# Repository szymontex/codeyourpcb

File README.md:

# CodeYourPCB

**Code-first PCB design.** Describe your circuit board in a simple DSL — get a deterministic, git-friendly, AI-editable design.

```cypcb
// blink.cypcb — 555 timer LED blink circuit
version 1

board blink {
    size 60mm x 40mm
    layers 2
}

component J1 connector "PIN-HDR-1x2" { value "5V PWR"; at 5mm, 20mm }
component U1 ic "SOIC-8" { value "NE555"; at 28mm, 20mm }
component R1 resistor "0402" { value "10k"; at 35mm, 30mm }
component C1 capacitor "1206" { value "10uF"; at 43mm, 20mm }
component LED1 led "0805" { value "RED"; at 55mm, 20mm }

net VCC [width 0.5mm  current 2A] { J1.1; U1.8; U1.4; R1.1 }
net GND { J1.2; U1.1; C1.2; LED1.K }

// Routed traces saved in the file — survives reload, diffs cleanly
trace VCC {
    layer Top
    width 0.5mm
    path 5mm,20mm -> 15mm,20mm -> 28mm,20mm -> 35mm,30mm
}
```

Save the file, board updates instantly. No compile step, no refresh.

**New here?** [Syntax reference](docs/SYNTAX.md) | [Getting started](docs/user-guide/getting-started.md) | [Examples](examples/)

---

## Why?

Traditional PCB tools (KiCad, Altium, Eagle) are GUI-first. The project file is a binary/XML side-effect of clicking. This makes:

- **Git diffs** unreadable
- **AI assistance** impractical
- **Team review** painful
- **Automation** fragile

CodeYourPCB flips the model: the source file _is_ the design. Text in, board out.

## The LLM angle

The core idea: give AI coding assistants like Claude Code, Copilot, or Cursor the ability to **design real PCBs through declarative code** — the same way they write software.

Traditional PCB formats are opaque to LLMs. A KiCad `.kicad_pcb` file is thousands of lines of coordinate soup. No LLM can reason about that meaningfully.

`.cypcb` is different — the semantics are declarative and human-readable:

```cypcb
component U1 ic "SOIC-8" { value "NE555"; at 28mm, 20mm }
net VCC [width 0.5mm  current 2A] { U1.8; U1.4; R1.1 }

trace VCC {
    layer Top
    width 0.5mm
    path 5mm,20mm -> 28mm,20mm -> 35mm,30mm
}
```

An LLM can generate this, review it, refactor it, and catch mistakes — just like source code. Even routed traces are human-readable `path` blocks that diff cleanly in git.

---

## Features

| Feature | Status |
|---------|--------|
| `.cypcb` DSL, read by a hand-written Rust parser | Done — the default since the C parser stopped reaching WASM; `--features tree-sitter-parser` builds the grammar instead and a differential test reads every example with both and compares the ASTs. `docs/one-parser.md` has the measurement behind the choice |
| Live preview — save file, board updates instantly | Done |
| 2D renderer (KiCad-style) | Done |
| 3D viewer — extruded copper, solder mask, round trace caps | Done |
| Interactive trace routing (45° constraint, obstacle dodge) | Done |
| Trace segment & corner editing (drag to reshape) | Done |
| Trace persistence — routed traces saved as `path` blocks, survive reload | Done |
| Bidirectional sync — edit trace code ↔ board updates in real-time | Done |
| Net constraints — `[width 0.5mm]`, `[current 2A]` per net | Done |
| IPC-2221 auto-width from current rating | Done |
| DRC — every rule in the registry: `grep -o 'Box::new(rules::[A-Za-z]*' crates/cypcb-drc/src/lib.rs` names them, because a list written here goes stale the next time one is added | Done — `grep -c 'Box::new(rules::' crates/cypcb-drc/src/lib.rs` counts them, because a number written here goes stale the next time one is added; `cypcb check` prints copper-on-copper apart from a gap under spec, gives an orphaned plane its size and corners, and says when a rule's number is this tool's own rather than the fab's |
| DRC — silkscreen clearance | Done — a Rust rule checks a footprint's own artwork against every other part's pads on the same side |
| Gerber / Excellon / BOM / pick-and-place export | Done — with a Gerber job file (`<board>-job.gbrjob`) at the root of the output, naming every Gerber and drill file, what each one is, its format and, for the images, its polarity - plus board size, layer count and, when the design declares a stackup, the material stackup and board thickness. Each file states its own function in its header and the job file reads it back, so the two cannot disagree |
| Monaco editor with context-aware completions | Done |
| JLCPCB parts search & placement | Done |
| Custom footprint definitions in DSL | Done |
| Project manager with templates | Done |
| Dark / Light theme | Done |
| Web app (WASM) | Done |
| Desktop app (Tauri v2) | Builds on macOS and Windows; the Linux build needs the GTK/webkit dev packages listed under Quick Start. Nothing here runs in CI, because there is none |
| Autorouter — PathFinder negotiated congestion, multi-layer | Routes the benchmark boards complete; **the toolbar button is hidden** while routing quality is worked on |
| KiCad component library import | Done |
| KiCad `.kicad_pcb` import | Done — `cypcb parse-kicad`, used by the routing benchmarks. Reads KiCad 5 through 10, including the tableless net form KiCad 10 introduced, where a pad names its net directly instead of pointing into a table |
| KiCad `.kicad_pcb` import to the language | Done — `cypcb from-kicad <board>.kicad_pcb` writes a `.cypcb` design: the board, a declared outline when it is not a plain rectangle, a `footprint` definition per part KiCad names, one `component` each with its value, placement, rotation and side, a `net` block per net, and the routed copper. The command re-reads what it wrote before reporting success. What a part *is* comes from its reference designator prefix, because KiCad does not record it, and `generic` where the prefix says nothing. A copper pour comes back as a `zone` block with the net and the layer it was poured on, named after that net where KiCad named it - `zone GND` bare and `zone "VBUS+"` quoted, because the language takes both; a board whose pads are named rather than numbered - a USB-C receptacle's A1, B4, S1 - comes back carrying those names, and a net called `VBUS+` or `D-` comes back quoted, because the language takes both and renaming either would move pins onto the wrong nets |
| KiCad `.kicad_pcb` export | Done — `cypcb to-kicad --preset <fab>` writes the outline, a footprint per part with its pads, nets and the face it is soldered to, every trace and via, the net list, every copper pour and keepout, the board thickness the design states, and a legend per part - its own artwork when the footprint has any, its courtyard outline when it does not, the same rule the Gerber writer follows. Free silkscreen text and 3D models are not written; KiCad fills its own defaults for what a file leaves out. With `--preset` it also writes the `.kicad_pro` beside the board, because that is where KiCad keeps design rules - a board file stating them is a board file pcbnew refuses to open. Open the board through that file and KiCad's own DRC measures it against the fab the design was checked for |
| Copper pour / ground planes | Done — a zone is filled against the copper on its layer, with the fab's clearance to foreign copper and thermal spokes to its own pads. The same geometry reaches the Gerbers, the viewer and the checker, which reports two planes shorted together and copper the fill left connected to nothing. See `examples/pour-island.cypcb` |
| Module system — reusable circuit blocks | Done — `module` defines one, `use M as N at 10mm, 5mm` places it, modules nest. See `examples/v2-modules.cypcb` |
| `import` — block libraries across files | Done — resolved relative to the importing file; modules, footprints and interfaces cross, a design's own board and parts do not. See `examples/v2-imports.cypcb` |
| `assert` — the design's own claims, checked | Done — `board.*`, `<part>.value` and `<net>.current/width/clearance`; anything else is reported as not checked rather than skipped |
| Parts engine — auto component picking from JLCPCB/LCSC | Partly — a design names the part with `lcsc "C7593"`, the viewer fetches that part's real footprint, and the bill of materials carries it in JLCPCB's own `LCSC Part #` column. Picking a part for you is planned |
| Two-sided assembly | Partly — `side bottom` on a component flips it onto the back of the board: its copper, solder mask, paste and silkscreen all move with it and the pick-and-place list says `Bottom`. The browser draws its legend in the bottom silkscreen colour and its pads on the bottom copper |
| Schematic generation from `.cypcb` | Planned |
| Differential pairs | Declared and checked — `diffpair USB { USB_DP USB_DM }`, and the checker measures the skew between the halves against the fab's length-match tolerance. Routing them alongside each other, and the gap between them, are still planned |
| CI/CD in GitHub Actions | Not planned — the quality gate is `scripts/quality-gate.sh`, run locally |

Routing quality on the six bundled KiCad benchmarks. The numbers move whenever
the router or the checker changes, so they are not written down here - this
prints them:

```bash
cargo test --release -p cypcb-autoroute --test benchmark_validation \
    -- benchmark_all_fixtures_drc --ignored --nocapture
```

Each line reads `N routes, V violations against R, S shorts against T, U
unrouted`, where `R` and `T` are ratchets: the values the board is not allowed
to exceed, declared in `DRC_RATCHETS` in that test and lowered as the router
improves. Every board routes to completion - `U` is 0 on all six, and that is
asserted, not observed.

A table of these numbers lived here and every row of it had gone stale: it
listed three of the six boards and figures the checker had since moved twice,
once by measuring copper instead of part bodies and once by seeing footprints
on imported boards at all. `docs/TRACKER.md` records each change with what it
moved.

`cypcb route` routes the board eleven ways and keeps the best,
because no one setting wins everywhere - measured across the six benchmark
boards, the winner differs between them. It costs roughly eleven times the wall
clock of a single run and buys, on `examples/blink.cypcb`, 2 violations with 2 shorts
against 4 with 3. `--fast` routes once when the wait matters more than the
board.

---

## Quick Start

### Web (development)

```bash
git clone https://github.com/szymontex/codeyourpcb.git
cd codeyourpcb
./scripts/setup-dev.sh   # Rust target, wasm-bindgen at the pinned version, binaryen, browsers

cd viewer
npm install
npm start                # builds WASM + starts dev server
```

**Prerequisites**: Rust (stable), Node.js 18+, and two tools the WASM build
runs directly - the `wasm-bindgen` CLI and `wasm-opt` from binaryen.
`./scripts/setup-dev.sh` installs both and is safe to run again; every step
checks before it installs. By hand:

```bash
# wasm-bindgen must match the version Cargo.lock pins, or the bindings it
# writes will not load the module the build produced.
cargo install wasm-bindgen-cli --version \
  "$(grep -A1 '^name = "wasm-bindgen"$' Cargo.lock | grep '^version' | cut -d'"' -f2)"

# binaryen, for wasm-opt. The build refuses to run without it rather than
# shipping a module a third larger.
sudo apt install binaryen     # Debian/Ubuntu
brew install binaryen         # macOS
```

`cargo binstall wasm-bindgen-cli --version ...` fetches a prebuilt binary where
`cargo install` compiles it from source; `cargo install
cargo-binstall` first, and fall back to `cargo install` on a platform it has no
build for.

**`wasm-pack` is not used.** `viewer/build-wasm.sh` runs cargo, wasm-bindgen
and wasm-opt as three steps of its own, because wasm-pack 0.14 cannot be told
about this project's `wasm-release` profile and runs a `wasm-opt -O` that
refuses the module. The script says so at the top.

Open http://localhost:4321 — pick a template or open a `.cypcb` file.

To reach that server from another machine, name the host it will answer to:
`CYPCB_DEV_HOSTS=board.example.lan npm start`. Vite refuses a `Host` header it
was not told about, and the list is empty by default, so without this you get a
bare 403 from your own dev server.

### Desktop app (Tauri)

```bash
# Linux prerequisites
sudo apt install libwebkit2gtk-4.1-dev libgtk-3-dev libayatana-appindicator3-dev librsvg2-dev pkg-config

npm run dev:desktop   # dev mode
npm run build:desktop # release installer
```

### CLI

```bash
cargo run -p cypcb-cli -- check examples/blink.cypcb          # DRC, exit 1 on violations
cargo run -p cypcb-cli -- export examples/blink.cypcb -o out    # refuses a shorted board unless --force
cargo run -p cypcb-cli -- route examples/blink.cypcb --variants   # route, keep the best
cargo run -p cypcb-cli -- score examples/blink.routed.cypcb   # quality metrics as JSON
cargo run -p cypcb-cli -- export examples/blink.cypcb         # 14 manufacturing files
cargo run -p cypcb-cli -- parse examples/blink.cypcb          # the board, as JSON
cargo run -p cypcb-cli -- parse examples/blink.cypcb -o ast    # the AST instead
cargo run -p cypcb-cli -- parse-kicad tests/fixtures/benchmark/led_blink.kicad_pcb   # a KiCad board
cargo run -p cypcb-cli -- to-kicad examples/blink.cypcb       # the design as a KiCad board
cargo run -p cypcb-cli -- from-kicad tests/fixtures/benchmark/led_blink.kicad_pcb   # a KiCad board as a design
cargo run -p cypcb-cli -- watch examples/blink.cypcb          # check again on every save
```

`check`, `route` and `score` all take `--preset`, and an unknown
name prints the list. Without it they read the board's own `fab`, for its layer
count; the `fab` section of `docs/SYNTAX.md` says which table that is. They use
the same rules and agree on the same board:
`examples/blink.routed.cypcb` is 2 violations to `check --preset pcbway` and 2
to `score --preset pcbway`.

On an **unrouted** file they will not agree, and that is not a disagreement
about the rules. `score` routes the board before measuring it, so it reports
what its own routing came to - `examples/blink.cypcb` is 24 violations to
`check` and 4 to `score`, because the second one laid copper first - three of
those four are corners the router drew itself.

`--preset` means two things, though, and the lists are not the same length.
`check`, `route` and `score` take a **design-rule** preset - what a house can
etch - and know eleven: `jlcpcb_standard_2layer`, `jlcpcb_standard_4layer`,
the two advanced variants, `pcbway_standard`, `oshpark_2layer`,
`oshpark_4layer`, `ipc_class1`, `ipc_class2`, `ipc_class3` and `prototype`,
with `jlcpcb`, `oshpark`, `pcbway` and `ipc1`..`ipc3` as short forms that name
what they resolved to. `export` takes a **file convention** preset - what a
house wants the Gerbers called and in what coordinate format - and only
`jlcpcb` and `pcbway` have been written down. So a board can be checked
against OSHPark and not yet exported for it; `cypcb export --house oshpark`
says exactly that.

### IDE workflow

Edit `.cypcb` files in your editor (VS Code, Neovim, etc.). Run `npm run dev:watch` in a terminal — the board preview updates on every save via WebSocket hot reload.

---

## Keyboard Shortcuts

| Key | Action |
|-----|--------|
| `Ctrl+E` | Toggle code editor |
| `Ctrl+S` | Save file |
| `Ctrl+O` | Open file / project manager |
| `Ctrl+J` | JLCPCB parts search |
| `Ctrl+Z` / `Ctrl+Shift+Z` | Undo / Redo |
| `F` | Fit board to view |
| `3` | Toggle 3D view |
| `R` / `Shift+R` | Rotate component CW / CCW |
| `?` | Keyboard shortcuts help |

During trace routing: `F` flip layer, `/` flip posture, `Q` toggle corner mode, `A` toggle angle snap.

---

## Project Structure

```
codeyourpcb/
├── crates/
│   ├── cypcb-core         # Types, coordinates, units
│   ├── cypcb-parser       # Rust reader (default) + Tree-sitter grammar
│   ├── cypcb-world        # ECS board state (bevy_ecs)
│   ├── cypcb-drc          # Design rule checks
│   ├── cypcb-autoroute    # A*-based autorouter (WIP)
│   ├── cypcb-router       # Route application, and the DSN/SES bridge
│   ├── cypcb-calc         # Electrical calculations (IPC-2221)
│   ├── cypcb-export       # Gerber / Excellon / CPL export
│   ├── cypcb-kicad        # KiCad format import and export
│   ├── cypcb-library      # Component library (SQLite + FTS5)
│   ├── cypcb-lsp          # Language server (tower-lsp)
│   ├── cypcb-render       # Board engine (WASM)
│   ├── cypcb-rules        # Design rules & manufacturer presets
│   ├── cypcb-platform     # Native/web abstraction layer
│   ├── cypcb-watcher      # File system watcher
│   └── cypcb-cli          # CLI entry point
├── viewer/                # TypeScript frontend (Vite + Canvas 2D + Three.js)
├── src-tauri/             # Tauri v2 desktop shell
├── examples/              # Sample .cypcb files
└── docs/                  # User guide, syntax, API reference
```

---

## Landscape

CodeYourPCB sits in the emerging "PCB as code" space alongside a few other tools:

- **[JITX](https://www.jitx.com/)** — commercial, most mature code-first EDA. Constraint-driven routing, signal integrity, VS Code integration. Proprietary.
- **[atopile](https://atopile.io/)** — open-source `.ato` language with compiler, reusable modules, component picking. Uses KiCad for layout. MIT.
- **[tscircuit](https://tscircuit.com/)** — open-source React/TypeScript PCB framework. Very LLM-friendly (TypeScript is natural for models). MIT.

Where CodeYourPCB differs: own rendering engine (no KiCad dependency), runs in browser via WASM, interactive routing built-in, traces persist as readable DSL code. Where it's behind: no schematic capture, smaller component library.

---

## Documentation

- [Getting Started](docs/user-guide/getting-started.md)
- [Language Syntax](docs/SYNTAX.md)
- [Architecture](docs/architecture.md)
- [Routing](docs/routing.md) - what the autorouter does, the settings that pay, and the seventeen measured and dropped
- [One parser](docs/one-parser.md) - why the language is read twice, what each way of fixing that costs, and which one was chosen
- [Project Structure](docs/user-guide/project-structure.md)
- [Library Management](docs/user-guide/library-management.md)
- [Platform Differences (Web vs Desktop)](docs/user-guide/platform-differences.md)
- [Language server](docs/language-server.md) - the `cypcb-lsp` binary: what it answers, what it does not, and how to point an editor at it
- [Editor features in the browser](docs/api/lsp-server.md) - the WASM bridge that gives the built-in editor its diagnostics, without a server process
- [Contributing](CONTRIBUTING.md)

---

## Status

Experimental. The DSL and file format may change between versions.

The core loop works: write `.cypcb` → see board → route traces → save → reload
→ export. Traces are deterministic and a saved board reads back as the board
it was, which is checked end to end: routed copper reaches the Gerbers, the
cut path matches the outline the source declares, the mask opens over every
pad and the pick-and-place names the side each part is assembled on.

A copper pour is filled by the engine and drawn from it: the viewer sends the
zones it parsed and gets back the rectangles a fabricator receives, so the
screen cannot disagree with the Gerber. Keepouts are outlined, and copper a
pour left stranded is outlined too, because an island looks exactly like the
rest of the plane.

The main gap is the autorouter: its toolbar button stays hidden while routing
quality is worked on. `interface` is no longer one - a module that claims an
interface nobody defined, or claims one and does not expose all of its pins, is
reported by name.

PRs welcome.

---

## License

Licensed under either of:

- [MIT License](LICENSE-MIT)
- [Apache License, Version 2.0](LICENSE-APACHE)

at your option.

Copyright 2026 Szymon Gwóźdź. See [NOTICE](NOTICE).

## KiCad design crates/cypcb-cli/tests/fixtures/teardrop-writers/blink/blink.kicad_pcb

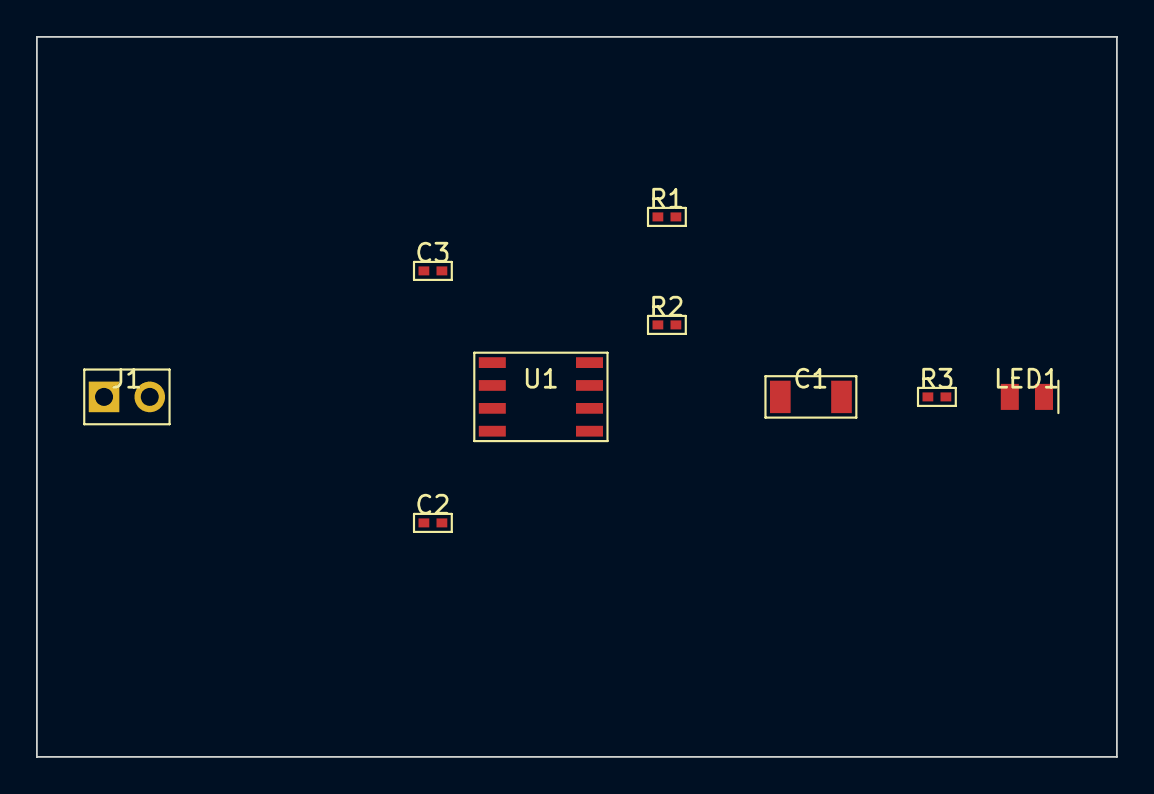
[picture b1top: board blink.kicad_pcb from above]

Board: 2 copper layers, 60.0 x 40.0 mm, 9 parts (0 on the bottom side), 7 nets, no tracks yet.

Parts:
C1: 10uF; 1206
C2, C3: 100nF; 0402
J1: 5V PWR; PIN-HDR-1x2
LED1: RED; LED_0805
R1: 10k; 0402
R2: 47k; 0402
R3: 470R; 0402
U1: NE555; SOIC-8

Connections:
CV: C2.1, U1.5
DIS: R1.2, R2.1, U1.7
GND: C1.2, C2.2, C3.2, J1.2, LED1.K, U1.1
LED_ANODE: LED1.A, R3.2
OUT: R3.1, U1.3
TRG_THR: C1.1, R2.2, U1.2, U1.6
VCC: C3.1, J1.1, R1.1, U1.4, U1.8

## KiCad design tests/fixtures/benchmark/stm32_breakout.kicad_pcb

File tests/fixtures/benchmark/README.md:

# Benchmark Fixtures

KiCad 8 PCB benchmark files for autorouter validation. Each file uses `(version 20240108)` format with the `footprint` keyword (KiCad 7/8 style).

## Fixtures

### led_blink.kicad_pcb — Simple

- **Source:** Synthetic (hand-crafted for benchmark suite)
- **License:** Same as project (MIT-equivalent)
- **Original project:** N/A — realistic LED blink circuit
- **Complexity tier:** Simple
- **Components:** 7 (1 connector, 1 switch, 2 capacitors, 2 resistors, 1 LED)
- **Nets:** 7 (VCC, GND, LED_ANODE, BATT_POS, SW_OUT, R_LED, BYPASS)
- **Layers:** 2 (F.Cu, B.Cu)
- **Board size:** 40×30 mm
- **Traces:** 3 segments, 2 vias

### stm32_breakout.kicad_pcb — Medium

- **Source:** Synthetic (hand-crafted for benchmark suite)
- **License:** Same as project (MIT-equivalent)
- **Original project:** N/A — realistic STM32F103C8T6 breakout board
- **Complexity tier:** Medium
- **Components:** 29 (1 MCU, 1 regulator, 1 USB-C, 1 ESD protection, 1 crystal, 1 switch, 2 GPIO headers, 1 SWD header, 11 capacitors, 7 resistors, 2 LEDs)
- **Nets:** 40 (power rails, GPIO PA0-PA7/PB0-PB7/PC13-PC15, USB, SWD, I2C, SPI, UART, ADC)
- **Layers:** 2 (F.Cu, B.Cu)
- **Board size:** 75×65 mm
- **Traces:** 8 segments, 4 vias

### multi_ic.kicad_pcb — Complex

- **Source:** Synthetic (hand-crafted for benchmark suite)
- **License:** Same as project (MIT-equivalent)
- **Original project:** N/A — realistic STM32F407 + Ethernet PHY + SPI Flash + CAN board
- **Complexity tier:** Complex
- **Components:** 52 (1 MCU LQFP-100, 1 Ethernet PHY QFN-24, 1 SPI Flash SOIC-8, 2 voltage regulators, 1 CAN transceiver, 1 USB ESD, 2 crystals, 1 Ethernet magnetics, 5 connectors, 1 ferrite bead, 1 reset switch, 5 LEDs, 12 resistors, 18 capacitors)
- **Nets:** 94 (3 power rails, 48 GPIO, USB, Ethernet RMII, SPI Flash, CAN, I2C, UART, SWD, ADC, oscillator)
- **Layers:** 4 (F.Cu, In1.Cu, In2.Cu, B.Cu)
- **Board size:** 100×80 mm
- **Traces:** 15 segments, 10 vias

### shift_driver.kicad_pcb — Medium

- **Source:** Generated by `make_shift_driver.py` in this directory
- **License:** Same as project (MIT-equivalent)
- **Original project:** N/A — three 74HC595 shift registers driving 24 LEDs
- **Complexity tier:** Medium
- **Components:** 55 (3 DIP-16 shift registers, 24 resistors, 24 LEDs, 3 bypass capacitors, 1 six-pin header)
- **Nets:** 55 (VCC, GND, SER, SRCLK, RCLK, 2 chain links, 24 drive, 24 anode)
- **Layers:** 2 (F.Cu, B.Cu)
- **Board size:** 68×48 mm
- **Traces:** none — it ships unrouted, which is what a routing benchmark wants

Added 2026-08-08. The three fixtures above are what every routing conclusion in
`docs/routing.md` was drawn from, and two of them are dense in the same way, so
a setting that happened to suit them could not be told from one that is right.
This board was generated rather than hand-placed so its provenance is
checkable: `make_shift_driver.py` declares the circuit as parts and nets and
knows nothing about the router. Through-hole DIP beside 0805 chips is a mix the
other three do not have.

It reports nothing but its own outline before routing — no courtyard overlap,
no pad-to-pad clearance, no mask bridge. The placement was spaced until that
was true, because a benchmark whose parts collide measures the router on a
board nobody would fabricate.

To regenerate: `python3 tests/fixtures/benchmark/make_shift_driver.py`

### qfp_fanout.kicad_pcb — Complex

- **Source:** Generated by `make_qfp_fanout.py` in this directory
- **License:** Same as project (MIT-equivalent)
- **Original project:** N/A — one LQFP-64 escaping to headers
- **Complexity tier:** Complex
- **Components:** 19 (1 LQFP-64, 11 capacitors, 2 resistors, 1 crystal, 4 twelve-pin headers, one per edge)
- **Nets:** 50 (VCC, GND, NRST, XTAL_IN, XTAL_OUT, BOOT, 44 GPIO)
- **Layers:** 2 (F.Cu, B.Cu)
- **Board size:** 46×46 mm
- **Traces:** none — it ships unrouted

Added 2026-08-08. The four boards above leave one regime untouched: a
fine-pitch part on two layers. `stm32_breakout` has a TQFP at 0.8mm pitch and
`multi_ic` an LQFP-100 on four layers with room to escape into; getting 64 pins
out at 0.5mm pitch with only a top and a bottom is what a two-layer router is
hardest on. It is the hardest of the five by some way — 665 introduced violations against
`multi_ic`'s 247 — and, like `shift_driver`, it reports nothing but its own
outline before routing.

Its first version put the GPIO on two twenty-one-pin headers down the sides.
That is 50.8mm of pins on a 46mm board, so three pads per header sat past the
outline and the router was being scored on a board nobody could make. A 46mm
edge holds fifteen pins once margins are taken, so two sides cannot hold
forty-eight: the headers are one per edge now, and no pad is outside the
outline.

Both generators share `kicad_emit.py`, which knows the file format and nothing
about the router.

To regenerate: `python3 tests/fixtures/benchmark/make_qfp_fanout.py`

### esp32_starter.cypcb - Medium, written in this language

- **Source:** Written by hand in `.cypcb`, not read from KiCad. The file's own header names the public datasheet behind every pin and value, with the date it was read
- **License:** Same as project (MIT-equivalent)
- **Original project:** N/A - an ESP32-S3-WROOM-1 starter board: USB-C in, AP2112K 3.3V regulator, BOOT and RESET buttons, two LEDs, two 1x12 GPIO headers
- **Complexity tier:** Medium
- **Components:** 18
- **Layers:** 2 (F.Cu, B.Cu)
- **Board size:** 34x50 mm
- **Traces:** none - the router lays them
- **Guarded by:** `cargo test -p cypcb-cli --test the_esp32_starter_is_a_board` - it parses, every part has a footprint, the module, receptacle and regulator pins are on the nets their datasheets name, and it routes. `cargo test -p cypcb-render --test esp32_starter_footprints_follow_their_datasheets` holds the four footprints to the figures of the pages the header cites, and `--test esp32_starter_routes_all_but_one_pin` holds the router to at most one open pin

## Usage

These files are parsed by `cypcb-kicad::pcb_parser::parse_kicad_pcb()` and used as benchmark inputs for:
- Parser correctness validation (`benchmark_parse.rs` integration tests)
- Autorouter performance benchmarking (S03/S07)
- Ratsnest extraction compatibility testing

## Format Notes

All files use KiCad 8 format (`version 20240108`) with:
- `footprint` keyword (not legacy `module`)
- `property` keyword for Reference/Value (not legacy `fp_text`)
- Realistic footprint library names (e.g., `Resistor_SMD:R_0402_1005Metric`)
- Proper layer assignments and net declarations

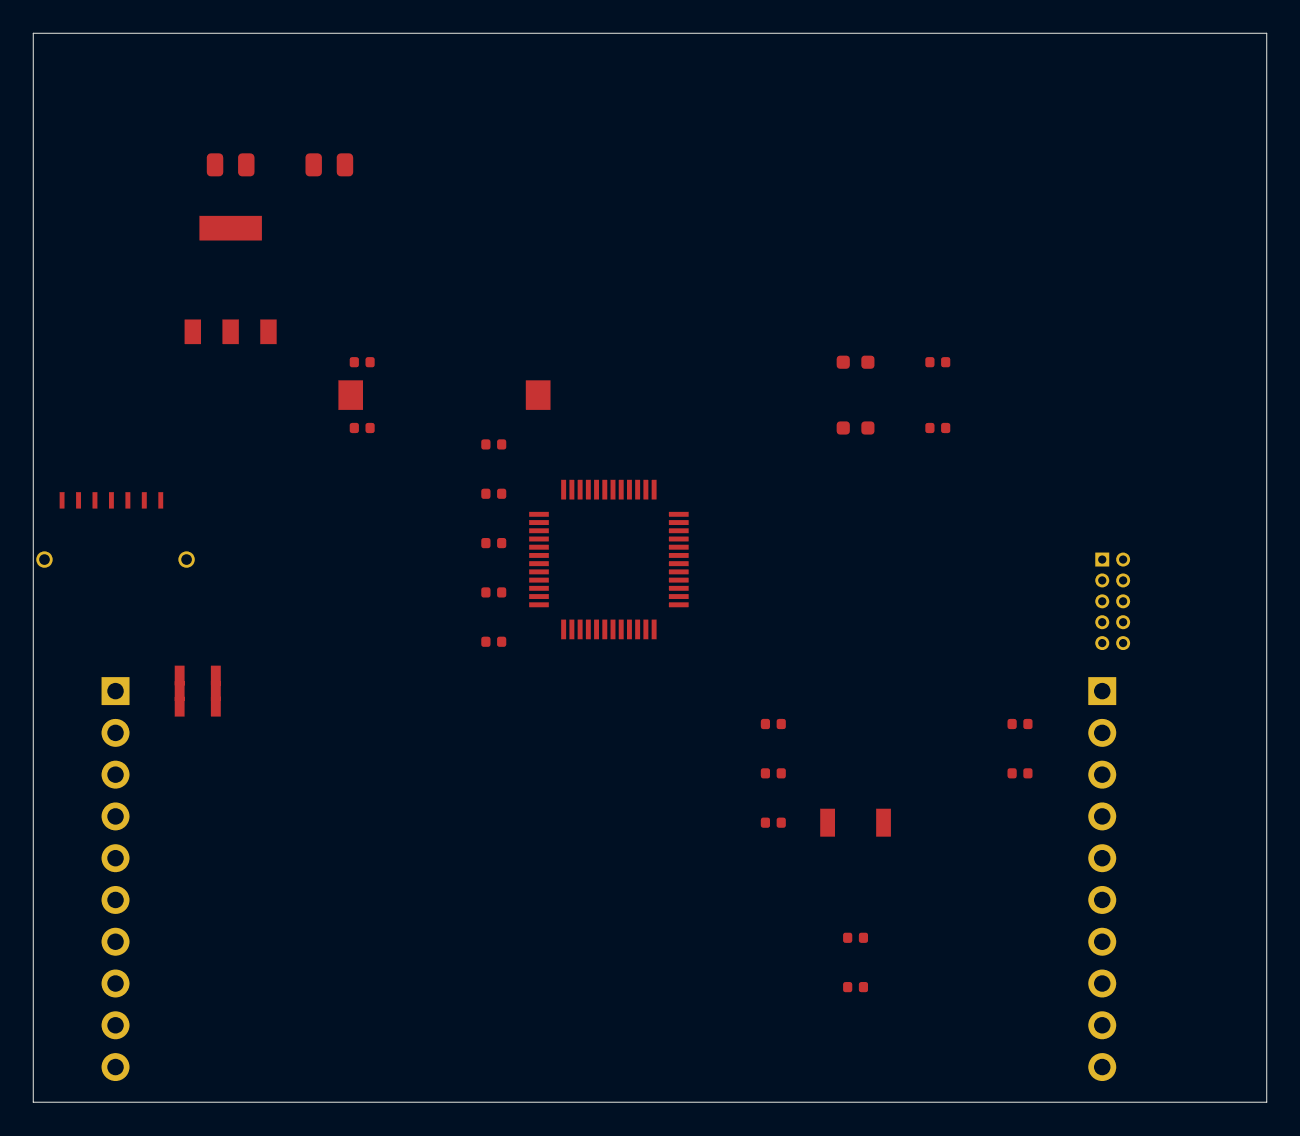
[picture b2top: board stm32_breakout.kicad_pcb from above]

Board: 2 copper layers, 75.0 x 65.0 mm, 29 parts (0 on the bottom side), 34 nets, no tracks yet.

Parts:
C1, C2, C3, C4, C10: 100nF; C_0402_1005Metric
C5: 4.7uF; C_0402_1005Metric
C6, C7: 20pF; C_0402_1005Metric
C8, C9: 10uF; C_0805_2012Metric
C11: 100pF; C_0402_1005Metric
D1: Green; LED_0603_1608Metric
D2: Blue; LED_0603_1608Metric
J1: USB_C; USB_C_Receptacle_HRO_TYPE-C-31-M-12
J2: SWD; PinHeader_2x05_P1.27mm_Vertical
J3: GPIO_L; PinHeader_1x10_P2.54mm_Vertical
J4: GPIO_R; PinHeader_1x10_P2.54mm_Vertical
R1, R2: 1k; R_0402_1005Metric
R3, R4: 10k; R_0402_1005Metric
R5, R6: 4.7k; R_0402_1005Metric
R7: 100; R_0402_1005Metric
SW1: RESET; SW_SPST_B3U-1000P
U1: STM32F103C8T6; LQFP-48_7x7mm_P0.5mm
U2: AMS1117-3.3; SOT-223-3_TabPin2
U3: USBLC6-2SC6; SOT-23-6
Y1: 8MHz; Crystal_SMD_HC49-SD

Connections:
ADC_IN: C11.1, R7.1, U1.29
BOOT0: R4.1, U1.19
GND: C1.2, C2.2, C3.2, C4.2, C5.2, C6.2, C7.2, C8.2, C9.2, C10.2, C11.2, J1.A1, J1.B1, J1.S1, J1.S2, J2.3, J2.5, J2.9, J3.2, J4.10, R4.2, SW1.2, U1.13, U1.21, U1.27, U1.46, U1.48, U2.1, U3.2
I2C_SCL: J4.9, R6.1, U1.36
I2C_SDA: J4.8, R5.1, U1.35
LED1_K: D1.2, R1.1, U1.43
LED2_K: D2.2, R2.1, U1.44
NRST: C10.1, J2.10, R3.1, SW1.1, U1.25
PA0: J3.3, R2.2, U1.2
PA1: J3.4, U1.3
PA2: J3.5, U1.4
PA3: J3.6, U1.5
PA4: J3.7, U1.6
PA5: J3.8, U1.7
PA6: J3.9, U1.8
PA7: J3.10, R7.2, U1.9
PB0: J4.1, U1.10
PB1: J4.2, U1.11
PB3: J4.3, U1.14
PB4: J4.4, U1.15
PB5: J4.5, U1.16
PB6: J4.6, U1.17
PB7: J4.7, U1.18
PC13: R1.2, U1.22
PC14: C6.1, U1.23, Y1.1
PC15: C7.1, U1.24, Y1.2
SWCLK: J2.4, U1.31
SWDIO: J2.2, U1.30
SWO: J2.6, U1.32
USB_DM: J1.A7, U1.42, U3.3, U3.4
USB_DP: J1.A6, U1.41, U3.1, U3.6
VBUS: C8.1, J1.A4, J1.B4, U1.1, U2.3, U3.5
VCC_3V3: C1.1, C2.1, C3.1, C5.1, C9.1, D1.1, D2.1, J2.1, J3.1, R3.2, R5.2, R6.2, U1.12, U1.20, U1.26, U1.45, U1.47, U2.2, U2.4
VDDA: C4.1, U1.28

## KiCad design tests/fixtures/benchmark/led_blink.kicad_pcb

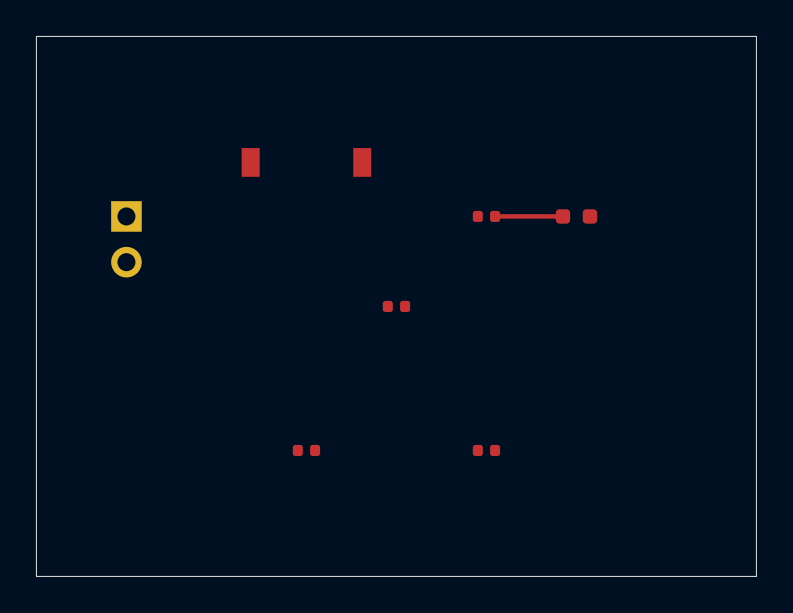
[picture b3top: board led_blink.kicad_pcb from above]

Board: 2 copper layers, 40.0 x 30.0 mm, 7 parts (0 on the bottom side), 5 nets.

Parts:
C1: 100nF; C_0402_1005Metric
C2: 10uF; C_0402_1005Metric
D1: Red; LED_0603_1608Metric
J1: Power; PinHeader_1x02_P2.54mm_Vertical
R1: 330; R_0402_1005Metric
R2: 10k; R_0402_1005Metric
SW1: ON/OFF; SW_SPST_CK_RS282G05A3

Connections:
BATT_POS: J1.1, SW1.1
GND: C1.2, C2.2, D1.2, J1.2
LED_ANODE: D1.1, R1.2
SW_OUT: C2.1, SW1.2
VCC: C1.1, R2.1

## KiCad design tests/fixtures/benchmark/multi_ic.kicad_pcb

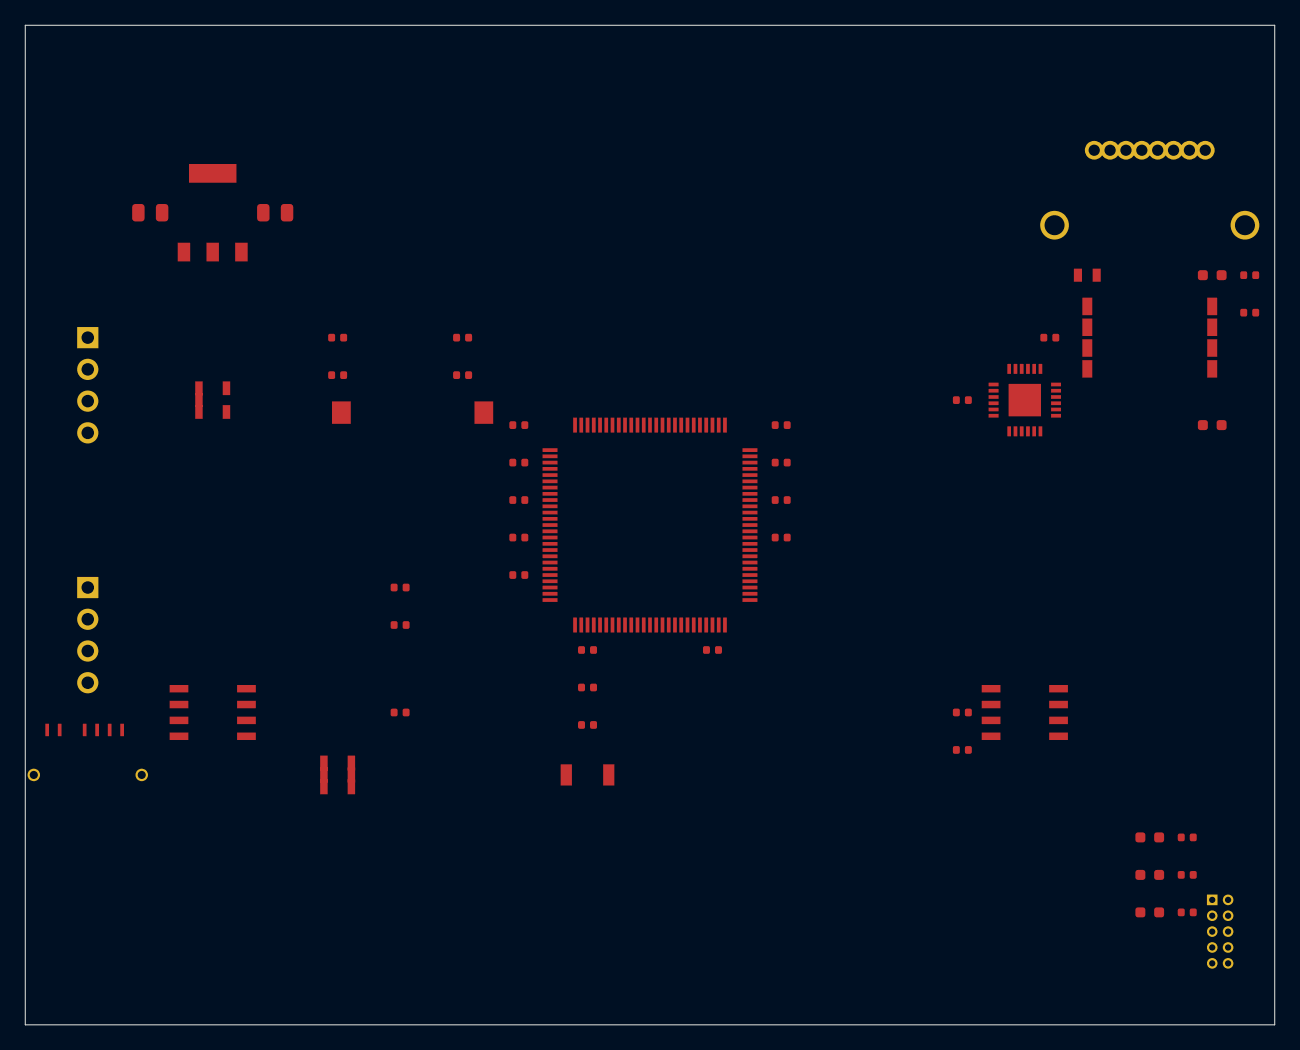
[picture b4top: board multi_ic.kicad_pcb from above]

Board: 4 copper layers, 100.0 x 80.0 mm, 52 parts (0 on the bottom side), 47 nets, no tracks yet.

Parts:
C1, C2, C3, C4, C5, C6, C7, C8, C9, C10, C11, C12, C13, C14, C15, C18: 100nF; C_0402_1005Metric
C16, C17: 22uF; C_0805_2012Metric
D1, D4: Green; LED_0603_1608Metric
D2: Red; LED_0603_1608Metric
D3: Blue; LED_0603_1608Metric
D5: Yellow; LED_0603_1608Metric
FB1: 600R@100MHz; L_0402_1005Metric
J1: USB_C; USB_C_Receptacle_HRO_TYPE-C-31-M-12
J2: RJ45; RJ45_Amphenol_54602-x08_Horizontal
J3: SWD; PinHeader_2x05_P1.27mm_Vertical
J4: CAN; PinHeader_1x04_P2.54mm_Vertical
J5: UART1; PinHeader_1x04_P2.54mm_Vertical
R1, R2, R3: 1k; R_0402_1005Metric
R4, R5: 330; R_0402_1005Metric
R6, R7: 10k; R_0402_1005Metric
R8, R9: 4.7k; R_0402_1005Metric
R10, R11: 22; R_0402_1005Metric
R12: 120; R_0402_1005Metric
SW1: RESET; SW_SPST_B3U-1000P
T1: 749010012A; Transformer_Ethernet_Wuerth_749010012A
U1: STM32F407VGT6; LQFP-100_14x14mm_P0.5mm
U2: LAN8720A; QFN-24-1EP_4x4mm_P0.5mm_EP2.6x2.6mm
U3: W25Q32JVSS; SOIC-8_3.9x4.9mm_P1.27mm
U4: AMS1117-3.3; SOT-223-3_TabPin2
U5: AP2112K-1.8; SOT-23-5
U6: SN65HVD230; SOIC-8_3.9x4.9mm_P1.27mm
U7: USBLC6-2SC6; SOT-23-6
Y1: 8MHz; Crystal_SMD_HC49-SD
Y2: 25MHz; Crystal_SMD_2012-2Pin_2.0x1.2mm

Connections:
BOOT0: R7.1, U1.56
CAN_RX: J4.4, R12.2, U1.87, U6.4
CAN_TX: J4.3, R12.1, U1.86, U6.1
ETH_LED_GREEN: D4.2, R4.1, U2.20
ETH_LED_YELLOW: D5.2, R5.1, U2.21
ETH_MDC: U1.83, U2.12
ETH_MDIO: U1.84, U2.13
ETH_REFCLK: C12.1, U1.85, U2.6, Y2.1
ETH_RXD0: U1.81, U2.8
ETH_RXD1: U1.82, U2.9
ETH_RXDV: U1.80, U2.7
ETH_RX_N: J2.6, T1.7, U2.17
ETH_RX_P: J2.3, T1.5, U2.16
ETH_TXD0: U1.78, U2.2
ETH_TXD1: U1.79, U2.3
ETH_TXEN: U1.77, U2.1
ETH_TX_N: J2.2, T1.3, U2.15
ETH_TX_P: J2.1, T1.1, U2.14
FLASH_CLK: U1.89, U3.6
FLASH_CS: U1.88, U3.1
FLASH_MISO: U1.91, U3.2
FLASH_MOSI: U1.90, U3.5
GND: C1.2, C2.2, C3.2, C4.2, C5.2, C6.2, C7.2, C8.2, C9.2, C10.2, C11.2, C12.2, C13.2, C14.2, C15.2, C16.2, C17.2, C18.2, J1.A1, J1.B1, J1.S1, J1.S2, J2.4, J2.5, J2.7, J2.8, J2.S1, J2.S2, J3.3, J3.5, J3.9, J4.2, J5.2, R4.2, R5.2, R7.2, SW1.2, T1.2, T1.6, U1.26, U1.52, U1.54, U1.64, U1.76, U1.93, U1.95, U1.97, U1.100, U2.5, U2.11, U2.19, U2.23, U2.25, U3.4, U4.1, U5.2, U5.3, U6.2, U6.5, U6.6, U6.7, U7.2, Y2.2
I2C1_SCL: R9.1, U1.70
I2C1_SDA: R8.1, U1.69
LED1_K: D1.2, R1.1
LED2_K: D2.2, R2.1
LED3_K: D3.2, R3.1
NRST: C18.1, J3.10, R6.1, SW1.1, U1.55, U2.24
OSC_IN: C10.1, U1.59, Y1.1
OSC_OUT: C11.1, U1.60, Y1.2
PA11: R11.2, U1.12
PA12: R10.2, U1.13
PA13: J3.2, U1.14
PA14: J3.4, U1.15
PA15: J3.6, U1.16
PC7: R1.2, U1.42
PC8: R2.2, U1.43
PC9: R3.2, U1.44
UART1_RX: J5.4, U1.66
UART1_TX: J5.3, U1.65
USB_DM: J1.A7, R11.1, U1.62, U7.3, U7.4
USB_DP: J1.A6, R10.1, U1.61, U7.1, U7.6
VCC_1V8: C8.1, U1.98, U5.4, U5.5
VCC_3V3: C1.1, C2.1, C3.1, C4.1, C5.1, C6.1, C7.1, C13.1, C14.1, C15.1, C17.1, D1.1, D2.1, D3.1, D4.1, D5.1, FB1.1, J3.1, J4.1, J5.1, R6.2, R8.2, R9.2, T1.4, T1.8, U1.25, U1.51, U1.53, U1.63, U1.75, U1.92, U1.94, U1.96, U1.99, U2.4, U2.10, U2.18, U2.22, U3.3, U3.7, U3.8, U4.2, U4.4, U5.1, U6.3, U6.8
VCC_5V: C16.1, J1.A4, J1.B4, U4.3, U7.5
VDDA: C9.1, FB1.2, U1.57

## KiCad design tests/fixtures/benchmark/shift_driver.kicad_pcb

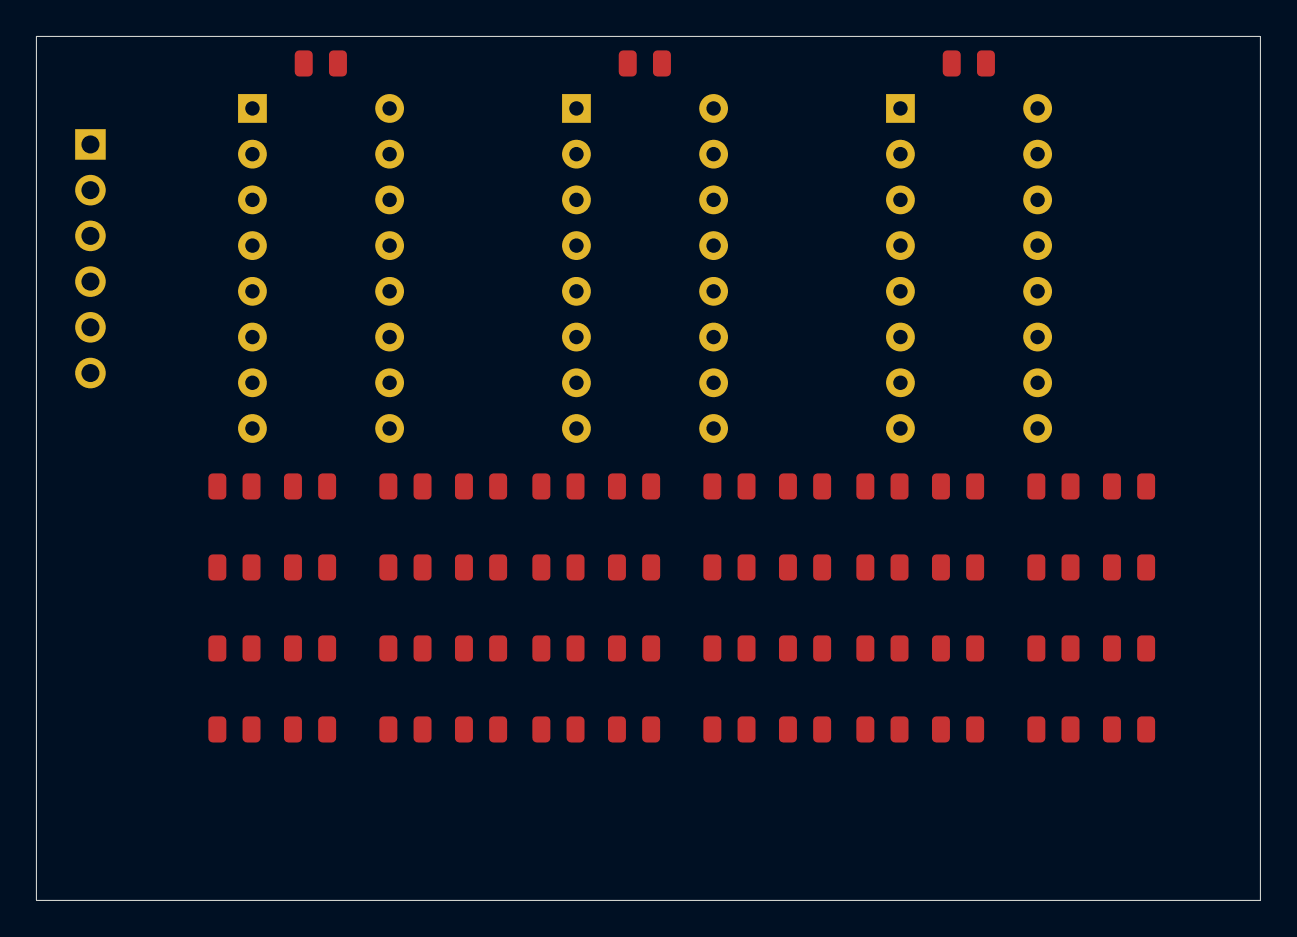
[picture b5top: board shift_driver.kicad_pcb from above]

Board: 2 copper layers, 68.0 x 48.0 mm, 55 parts (0 on the bottom side), 55 nets, no tracks yet.

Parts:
C1, C2, C3: 100nF; R_0805_2012Metric
D1, D2, D3, D4, D5, D6, D7, D8, D9, D10, D11, D12, D13, D14, D15, D16, D17, D18, D19, D20, D21, D22, D23, D24: RED; R_0805_2012Metric
J1: Ctrl; PinHeader_1x06_P2.54mm_Vertical
R1, R2, R3, R4, R5, R6, R7, R8, R9, R10, R11, R12, R13, R14, R15, R16, R17, R18, R19, R20, R21, R22, R23, R24: 330R; R_0805_2012Metric
U1, U2, U3: 74HC595; DIP-16_W7.62mm

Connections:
A0: D1.1, R1.2
A1: D2.1, R2.2
A2: D3.1, R3.2
A3: D4.1, R4.2
A4: D5.1, R5.2
A5: D6.1, R6.2
A6: D7.1, R7.2
A7: D8.1, R8.2
A8: D9.1, R9.2
A9: D10.1, R10.2
A10: D11.1, R11.2
A11: D12.1, R12.2
A12: D13.1, R13.2
A13: D14.1, R14.2
A14: D15.1, R15.2
A15: D16.1, R16.2
A16: D17.1, R17.2
A17: D18.1, R18.2
A18: D19.1, R19.2
A19: D20.1, R20.2
A20: D21.1, R21.2
A21: D22.1, R22.2
A22: D23.1, R23.2
A23: D24.1, R24.2
CHAIN1: U1.9, U2.14
CHAIN2: U2.9, U3.14
GND: C1.2, C2.2, C3.2, D1.2, D2.2, D3.2, D4.2, D5.2, D6.2, D7.2, D8.2, D9.2, D10.2, D11.2, D12.2, D13.2, D14.2, D15.2, D16.2, D17.2, D18.2, D19.2, D20.2, D21.2, D22.2, D23.2, D24.2, J1.2, J1.6, U1.8, U1.13, U2.8, U2.13, U3.8, U3.9, U3.13
Q0: R1.1, U1.15
Q1: R2.1, U1.1
Q2: R3.1, U1.2
Q3: R4.1, U1.3
Q4: R5.1, U1.4
Q5: R6.1, U1.5
Q6: R7.1, U1.6
Q7: R8.1, U1.7
Q8: R9.1, U2.15
Q9: R10.1, U2.1
Q10: R11.1, U2.2
Q11: R12.1, U2.3
Q12: R13.1, U2.4
Q13: R14.1, U2.5
Q14: R15.1, U2.6
Q15: R16.1, U2.7
Q16: R17.1, U3.15
Q17: R18.1, U3.1
Q18: R19.1, U3.2
Q19: R20.1, U3.3
Q20: R21.1, U3.4
Q21: R22.1, U3.5
Q22: R23.1, U3.6
Q23: R24.1, U3.7
RCLK: J1.5, U1.12, U2.12, U3.12
SER: J1.3, U1.14
SRCLK: J1.4, U1.11, U2.11, U3.11
VCC: C1.1, C2.1, C3.1, J1.1, U1.10, U1.16, U2.10, U2.16, U3.10, U3.16
